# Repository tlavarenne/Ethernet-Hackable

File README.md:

# Ethernet-Hackable
Fichiers Python et acquisitions (CSV et bin) liées à l'article "Ethernet à la loupe: de la couche physique au décodage des trames" du magazine Hackable n°61 juillet/août 2025, Editions Diamond.
https://boutique.ed-diamond.com/parution/4-hackable

# Ethernet 10BASE-T:

L'étude du protocole 10BASE-T décrite dans l'article a conduit à la création d'une interface graphique pyQT5 pour décoder les trames Ethernet.

script: decode_ethernet_10Mbps_Interface_Graphique.py

Les fichiers CSV sont à télécharger séparément. Bien sélectionner le bon modèle d'oscilloscope en rapport avec le fichier CSV à décoder.

Vidéo démonstration:

https://drive.google.com/file/d/1IcIyn7spNMZc0p1wGvt3BzvhHJLoFkX5/view?usp=drive_link

# Ethernet 100BASE-TX: 

Deux scripts sont fournis, un dans lequel les fichiers à charger sont à indiquer manuellement dans le fichier (éditeur python nécéssaire), un autre permettant l'execution en passant en argument le nom de fichier et éventuellement les paramètres nécéssaires:

- decode_ethernet100Mbps_avec_synchro_V10.py qui reprend l'intégralité du traitement décrit dans l'article Hackable en y rajoutant la resynchronisation en cas de perte du LFSR ainsi que l'analyse des trames avec SCAPY (https://scapy.net), module python à installer (sinon modifier la ligne 395 dans le script ANALYSE_SCAPY == False).

Ce script est à ouvrir avec un éditeur de fichier et il s'agit de modifier à la main le nom et le chemin des fichiers à traiter avant de l'executer.

- decode_ethernet100Mbps_avec_synchro_V10_AVEC_ARGUMENT.py qui permet une execution directement en passant les arguments nécéssaires:

  -f nom_du_fichier
  
  -s sampling_rate           (*fichiers binaires JMF uniquement*)
  
  -c voie 1 ou 2 si entrelacées       (*fichiers binaires JMF uniquement*)

**Exemples d'appel:**

python decode_ethernet100Mbps_avec_synchro_V10_AVEC_ARGUMENT.py -f Tek0004.csv   # pour un fichier CSV

python decode_ethernet100Mbps_avec_synchro_V10_AVEC_ARGUMENT.py -f CUT_RefCurve_2025-04-25_0_154619_1GSps_ping10ms.Wfm.bin -s 1e9 -c 2   # pour un fichier binaire JMF

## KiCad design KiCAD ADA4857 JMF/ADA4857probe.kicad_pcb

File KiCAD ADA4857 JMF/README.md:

Fichiers KiCAD pour réaliser la sonde différentielle proposée par Jean-Michel Friedt dans son complément à l'article.

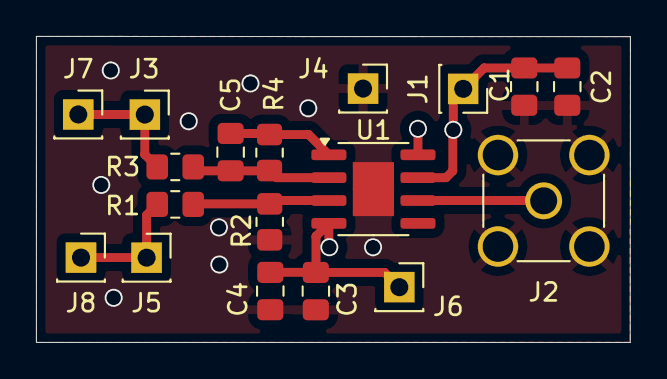
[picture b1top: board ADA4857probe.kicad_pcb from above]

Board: 2 copper layers, 33.0 x 17.0 mm, 18 parts (0 on the bottom side), 9 nets.

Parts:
C1, C2, C3, C4, C5: C; C_0805_2012Metric_Pad1.18x1.45mm_HandSolder
J1, J3, J4, J5, J6, J7, J8: Conn_01x01_Pin; PinSocket_1x01_P2.54mm_Vertical
J2: Conn_Coaxial; SMA_Amphenol_901-144_Vertical
R1, R2, R3, R4: R; R_0805_2012Metric_Pad1.20x1.40mm_HandSolder
U1: ADA4817; SOIC-8-1EP_3.9x4.9mm_P1.27mm_EP2.29x3mm

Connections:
+VSW: C1.1, C2.1, J1.1, U1.7 (+V_{S}), U1.8 (~PD)
-VSW: C3.1, C4.1, J6.1, U1.4 (-V_{S})
GND: C1.2, C2.2, C3.2, C4.2, J2.2 (Ext), J4.1, R2.1, U1.9 (EP)
unnamed: J2.1 (In), U1.6
unnamed: J3.1, J7.1, R3.1
unnamed: J5.1, J8.1, R1.1
unnamed: R1.2, R2.2, U1.3 (+)
unnamed: C5.1, R3.2, R4.1, U1.2 (-)
unnamed: C5.2, R4.2, U1.1 (FB)

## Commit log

2025-04-29 Fichiers acquisitions CSV
2025-05-10 Create KiCAD ADA4857 JMF
